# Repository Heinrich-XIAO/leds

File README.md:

# My First PCB
This is my first PCB. Yay!! I hope it doesn't make magic smoke.

## Schematic

## PCB

## Features
Two buttons that should turn the leds on when pushed.

## BOM
- Two Push Buttons
- A battery cell
- Two LEDs
- Two resistors 100ohm

Made with skill issues by `@itsme` on slack.

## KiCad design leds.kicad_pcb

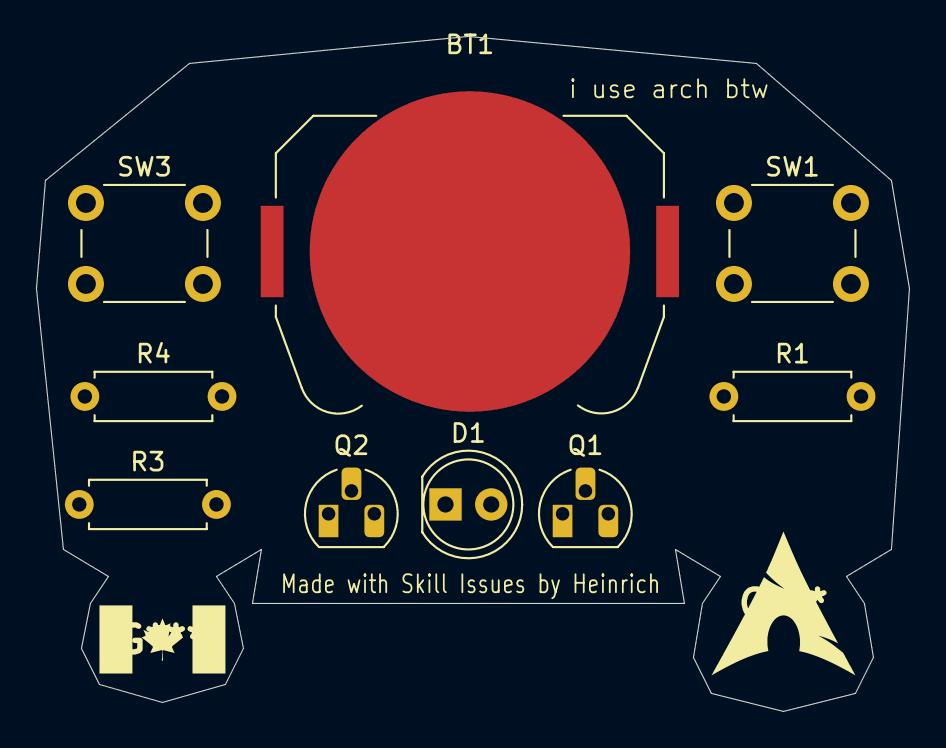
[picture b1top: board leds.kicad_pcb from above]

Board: 2 copper layers, 48.5 x 37.5 mm, 9 parts (0 on the bottom side), 9 nets, no tracks yet.

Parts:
BT1: Battery_Cell; BatteryHolder_Keystone_3034_1x20mm
D1: LED; LED_D5.0mm
Q1, Q2: NPN; TO-92L_HandSolder
R1, R3, R4: R; R_Axial_DIN0207_L6.3mm_D2.5mm_P7.62mm_Horizontal
SW1, SW3: SW_Push; SW_PUSH_6mm

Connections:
unnamed: BT1.1 (+), R1.1, SW1.1, SW3.1
unnamed: BT1.2 (-), Q1.3 (E)
unnamed: D1.2 (A), R1.2
unnamed: D1.1 (K), Q2.1 (C)
unnamed: Q1.2 (B), R4.2
unnamed: Q1.1 (C), Q2.3 (E)
unnamed: Q2.2 (B), R3.2
unnamed: R3.1, SW3.2
unnamed: R4.1, SW1.2

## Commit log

2025-06-01 stuff
2025-06-01 clean
2025-06-01 readme
2025-06-01 screenshots
2025-06-01 add my authorship
2025-06-01 new thing
2025-06-01 images
